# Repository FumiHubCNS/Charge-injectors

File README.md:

# Charge-injectors
Charge injectors for front-end cards

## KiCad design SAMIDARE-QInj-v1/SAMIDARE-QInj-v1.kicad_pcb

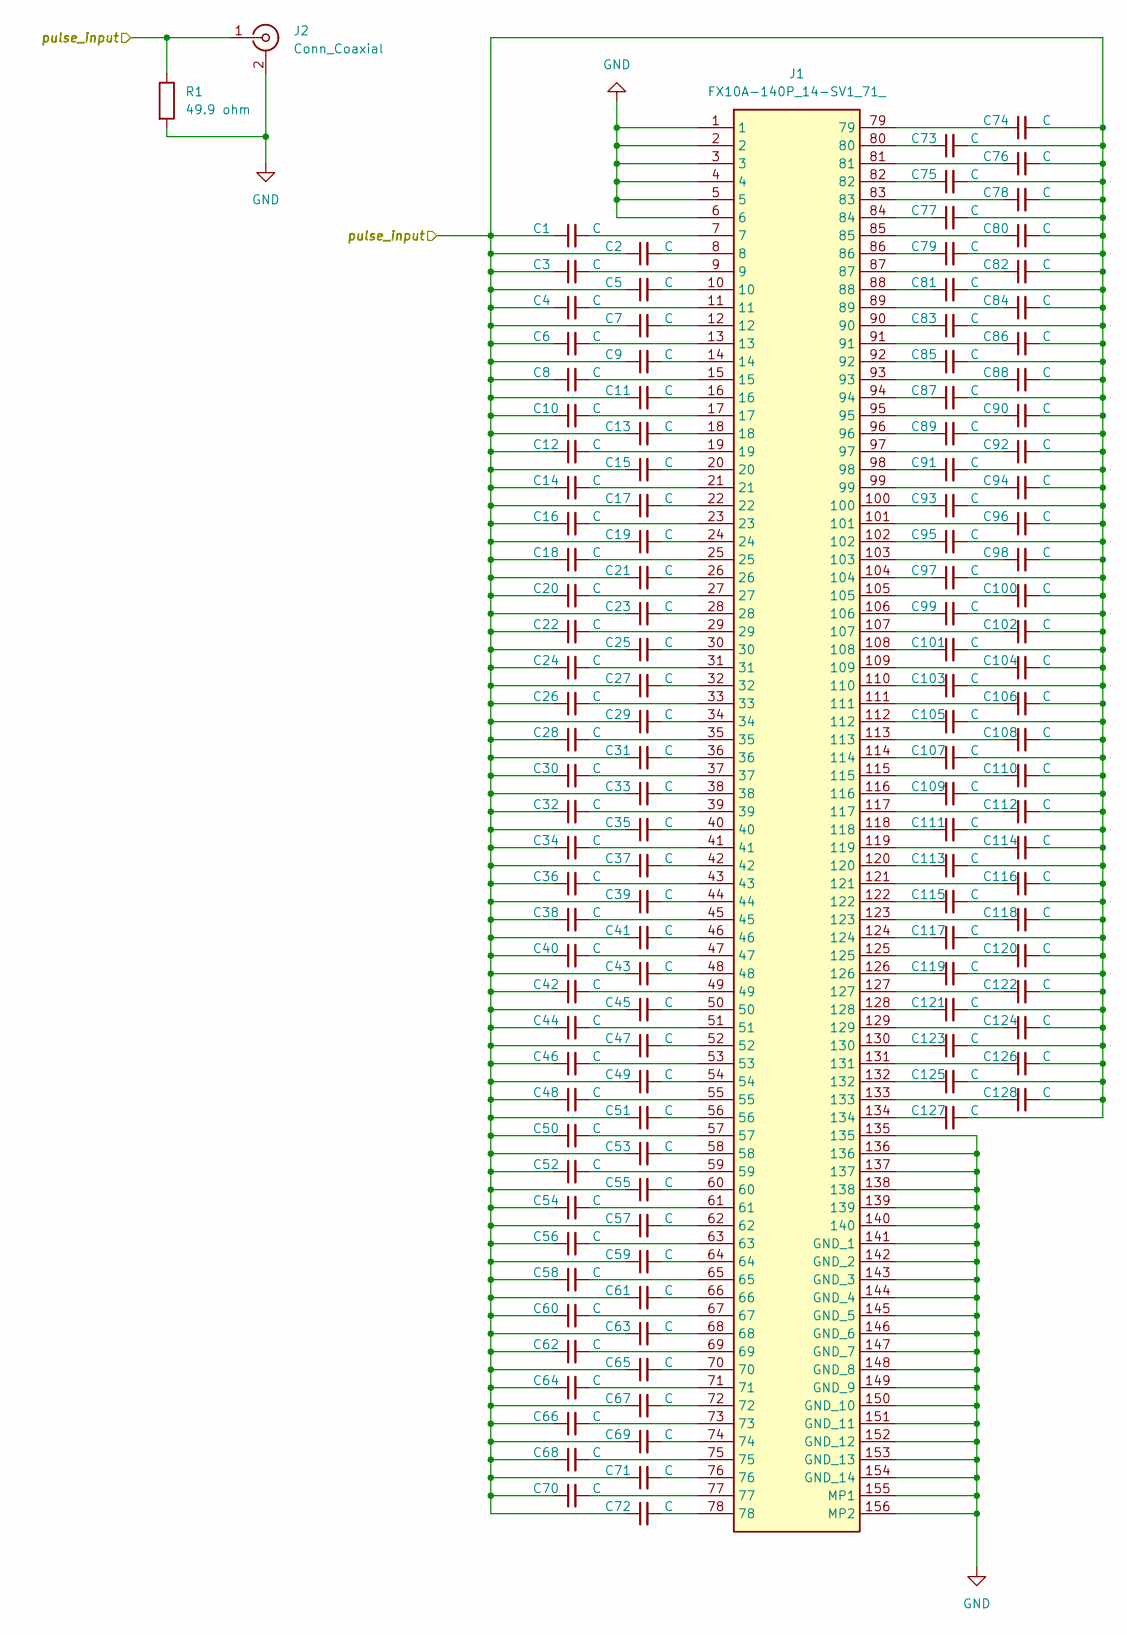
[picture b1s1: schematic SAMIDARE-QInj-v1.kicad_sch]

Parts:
C1, C2, C3, C4, C5, C6, C7, C8, C9, C10, C11, C12, C13, C14, C15, C16, C17, C18, C19, C20, C21, C22, C23, C24, C25, C26, C27, C28, C29, C30, C31, C32, C33, C34, C35, C36, C37, C38, C39, C40, C41, C42, C43, C44, C45, C46, C47, C48, C49, C50, C51, C52, C53, C54, C55, C56, C57, C58, C59, C60, C61, C62, C63, C64, C65, C66, C67, C68, C69, C70, C71, C72, C73, C74, C75, C76, C77, C78, C79, C80, C81, C82, C83, C84, C85, C86, C87, C88, C89, C90, C91, C92, C93, C94, C95, C96, C97, C98, C99, C100, C101, C102, C103, C104, C105, C106, C107, C108, C109, C110, C111, C112, C113, C114, C115, C116, C117, C118, C119, C120, C121, C122, C123, C124, C125, C126, C127, C128: C; C_0402_1005Metric
J1: FX10A-140P_14-SV1_71_; FX10A140P14SV171; Manufacturer_Part_Number FX10A-140P/14-SV1(71); Mouser Part Number 798-FX10A140P14SV171
J2: Conn_Coaxial; MMCX_Molex_73415-0961_Horizontal_1.6mm-PCB
R1: 49.9 ohm; R_0603_1608Metric

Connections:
/pulse_input: C1.1, C2.1, C3.1, C4.1, C5.1, C6.1, C7.1, C8.1, C9.1, C10.1, C11.1, C12.1, C13.1, C14.1, C15.1, C16.1, C17.1, C18.1, C19.1, C20.1, C21.1, C22.1, C23.1, C24.1, C25.1, C26.1, C27.1, C28.1, C29.1, C30.1, C31.1, C32.1, C33.1, C34.1, C35.1, C36.1, C37.1, C38.1, C39.1, C40.1, C41.1, C42.1, C43.1, C44.1, C45.1, C46.1, C47.1, C48.1, C49.1, C50.1, C51.1, C52.1, C53.1, C54.1, C55.1, C56.1, C57.1, C58.1, C59.1, C60.1, C61.1, C62.1, C63.1, C64.1, C65.1, C66.1, C67.1, C68.1, C69.1, C70.1, C71.1, C72.1, C73.2, C74.2, C75.2, C76.2, C77.2, C78.2, C79.2, C80.2, C81.2, C82.2, C83.2, C84.2, C85.2, C86.2, C87.2, C88.2, C89.2, C90.2, C91.2, C92.2, C93.2, C94.2, C95.2, C96.2, C97.2, C98.2, C99.2, C100.2, C101.2, C102.2, C103.2, C104.2, C105.2, C106.2, C107.2, C108.2, C109.2, C110.2, C111.2, C112.2, C113.2, C114.2, C115.2, C116.2, C117.2, C118.2, C119.2, C120.2, C121.2, C122.2, C123.2, C124.2, C125.2, C126.2, C127.2, C128.2, J2.1 (In), R1.1
GND: J1.1, J1.2, J1.3, J1.4, J1.5, J1.6, J1.135, J1.136, J1.137, J1.138, J1.139, J1.140, J1.141 (GND_1), J1.142 (GND_2), J1.143 (GND_3), J1.144 (GND_4), J1.145 (GND_5), J1.146 (GND_6), J1.147 (GND_7), J1.148 (GND_8), J1.149 (GND_9), J1.150 (GND_10), J1.151 (GND_11), J1.152 (GND_12), J1.153 (GND_13), J1.154 (GND_14), J1.155 (MP1), J1.156 (MP2), J2.2 (Ext), R1.2
unnamed: C1.2, J1.7
unnamed: C2.2, J1.8
unnamed: C3.2, J1.9
unnamed: C4.2, J1.11
unnamed: C5.2, J1.10
unnamed: C6.2, J1.13
unnamed: C7.2, J1.12
unnamed: C8.2, J1.15
unnamed: C9.2, J1.14
unnamed: C10.2, J1.17
unnamed: C11.2, J1.16
unnamed: C12.2, J1.19
unnamed: C13.2, J1.18
unnamed: C14.2, J1.21
unnamed: C15.2, J1.20
unnamed: C16.2, J1.23
unnamed: C17.2, J1.22
unnamed: C18.2, J1.25
unnamed: C19.2, J1.24
unnamed: C20.2, J1.27
unnamed: C21.2, J1.26
unnamed: C22.2, J1.29
unnamed: C23.2, J1.28
unnamed: C24.2, J1.31
unnamed: C25.2, J1.30
unnamed: C26.2, J1.33
unnamed: C27.2, J1.32
unnamed: C28.2, J1.35
unnamed: C29.2, J1.34
unnamed: C30.2, J1.37
unnamed: C31.2, J1.36
unnamed: C32.2, J1.39
unnamed: C33.2, J1.38
unnamed: C34.2, J1.41
unnamed: C35.2, J1.40
unnamed: C36.2, J1.43
unnamed: C37.2, J1.42
unnamed: C38.2, J1.45
unnamed: C39.2, J1.44
unnamed: C40.2, J1.47
unnamed: C41.2, J1.46
unnamed: C42.2, J1.49
unnamed: C43.2, J1.48
unnamed: C44.2, J1.51
unnamed: C45.2, J1.50
unnamed: C46.2, J1.53
unnamed: C47.2, J1.52
unnamed: C48.2, J1.55
unnamed: C49.2, J1.54
unnamed: C50.2, J1.57
unnamed: C51.2, J1.56
unnamed: C52.2, J1.59
unnamed: C53.2, J1.58
unnamed: C54.2, J1.61
unnamed: C55.2, J1.60
unnamed: C56.2, J1.63
unnamed: C57.2, J1.62
unnamed: C58.2, J1.65
unnamed: C59.2, J1.64
unnamed: C60.2, J1.67
unnamed: C61.2, J1.66
unnamed: C62.2, J1.69
unnamed: C63.2, J1.68
unnamed: C64.2, J1.71
unnamed: C65.2, J1.70
unnamed: C66.2, J1.73
unnamed: C67.2, J1.72
unnamed: C68.2, J1.75
unnamed: C69.2, J1.74
unnamed: C70.2, J1.77
unnamed: C71.2, J1.76
unnamed: C72.2, J1.78
unnamed: C73.1, J1.80
unnamed: C74.1, J1.79
unnamed: C75.1, J1.82
unnamed: C76.1, J1.81
unnamed: C77.1, J1.84
unnamed: C78.1, J1.83
unnamed: C79.1, J1.86
unnamed: C80.1, J1.85
unnamed: C81.1, J1.88
unnamed: C82.1, J1.87
unnamed: C83.1, J1.90
unnamed: C84.1, J1.89
unnamed: C85.1, J1.92
unnamed: C86.1, J1.91
unnamed: C87.1, J1.94
unnamed: C88.1, J1.93
unnamed: C89.1, J1.96
unnamed: C90.1, J1.95
unnamed: C91.1, J1.98
unnamed: C92.1, J1.97
unnamed: C93.1, J1.100
unnamed: C94.1, J1.99
unnamed: C95.1, J1.102
unnamed: C96.1, J1.101
unnamed: C97.1, J1.104
unnamed: C98.1, J1.103
unnamed: C99.1, J1.106
unnamed: C100.1, J1.105
unnamed: C101.1, J1.108
unnamed: C102.1, J1.107
unnamed: C103.1, J1.110
unnamed: C104.1, J1.109
unnamed: C105.1, J1.112
unnamed: C106.1, J1.111
unnamed: C107.1, J1.114
unnamed: C108.1, J1.113
unnamed: C109.1, J1.116
unnamed: C110.1, J1.115
unnamed: C111.1, J1.118
unnamed: C112.1, J1.117
unnamed: C113.1, J1.120
unnamed: C114.1, J1.119
unnamed: C115.1, J1.122
unnamed: C116.1, J1.121
unnamed: C117.1, J1.124
unnamed: C118.1, J1.123
unnamed: C119.1, J1.126
unnamed: C120.1, J1.125
unnamed: C121.1, J1.128
unnamed: C122.1, J1.127
unnamed: C123.1, J1.130
unnamed: C124.1, J1.129
unnamed: C125.1, J1.132
unnamed: C126.1, J1.131
unnamed: C127.1, J1.134
unnamed: C128.1, J1.133

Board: 2 copper layers, 131 parts (1 on the bottom side), 130 nets, no tracks yet.

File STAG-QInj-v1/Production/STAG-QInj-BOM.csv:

Designator,Footprint,Quantity,Comment,LCSC Part #
"J1","SAMTEC_QTE-040-01-L-D-A",1,"QTE-040-01-L-D-A",C3642632
"C17,C14,C32,C16,C2,C11,C64,C20,C10,C4,C38,C5,C63,C7,C59,C61,C50,C18,C13,C34,C19,C54,C24,C51,C15,C42,C60,C45,C23,C41,C28,C46,C29,C9,C27,C36,C49,C56,C53,C40,C55,C52,C62,C35,C48,C6,C57,C39,C21,C8,C22,C58,C26,C12,C1,C33,C47,C25,C43,C44,C3,C30,C31,C37","C_0402_1005Metric",64,"1pF, 1005, Tolerance +- 10%",C76953
"R1","R_0603_1608Metric",1,"49.9Ω, 1608, Tolerance +- 1%",C23185
"J2","SAMTEC_MMCX-J-P-H-ST-EM1",1,"MMCX",C5670146

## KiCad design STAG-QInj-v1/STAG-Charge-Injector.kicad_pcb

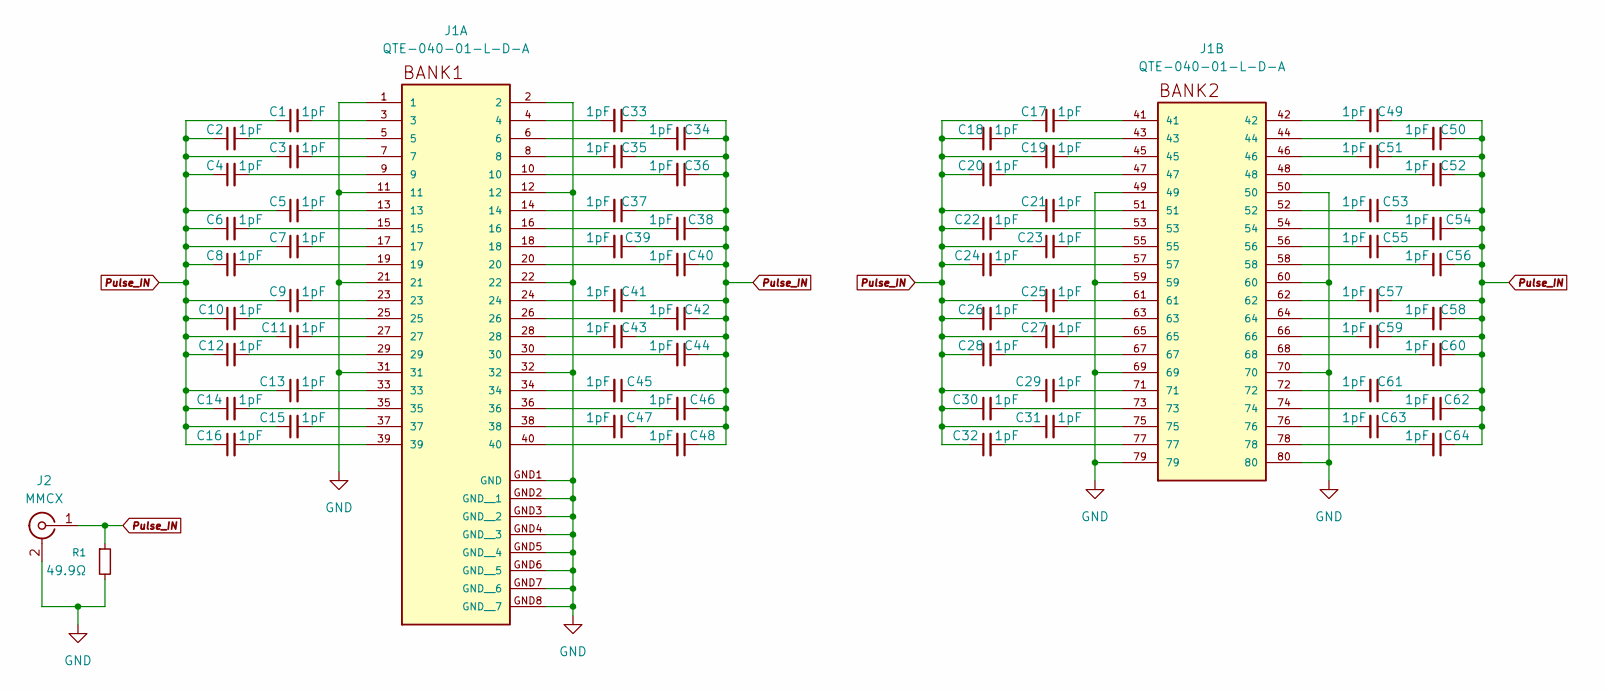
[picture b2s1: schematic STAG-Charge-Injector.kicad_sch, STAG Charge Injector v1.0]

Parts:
C1, C2, C3, C4, C5, C6, C7, C8, C9, C10, C11, C12, C13, C14, C15, C16, C17, C18, C19, C20, C21, C22, C23, C24, C25, C26, C27, C28, C29, C30, C31, C32, C33, C34, C35, C36, C37, C38, C39, C40, C41, C42, C43, C44, C45, C46, C47, C48, C49, C50, C51, C52, C53, C54, C55, C56, C57, C58, C59, C60, C61, C62, C63, C64: 1pF; C_0402_1005Metric
J1: QTE-040-01-L-D-A; SAMTEC_QTE-040-01-L-D-A; PARTREV CM
J2: MMCX; SAMTEC_MMCX-J-P-H-ST-EM1
R1: 49.9Ω; R_0603_1608Metric

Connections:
GND: J1.1, J1.2, J1.11, J1.12, J1.21, J1.22, J1.31, J1.32, J1.49, J1.50, J1.59, J1.60, J1.69, J1.70, J1.79, J1.80, J1.GND1 (GND), J1.GND2 (GND__1), J1.GND3 (GND__2), J1.GND4 (GND__3), J1.GND5 (GND__4), J1.GND6 (GND__5), J1.GND7 (GND__6), J1.GND8 (GND__7), J2.2 (Ext), J2.S1, J2.S2, R1.2
unnamed: C1.2, J1.3
unnamed: C2.2, J1.5
unnamed: C3.2, J1.7
unnamed: C4.2, J1.9
unnamed: C5.2, J1.13
unnamed: C6.2, J1.15
unnamed: C7.2, J1.17
unnamed: C8.2, J1.19
unnamed: C9.2, J1.23
unnamed: C10.2, J1.25
unnamed: C11.2, J1.27
unnamed: C12.2, J1.29
unnamed: C13.2, J1.33
unnamed: C14.2, J1.35
unnamed: C15.2, J1.37
unnamed: C16.2, J1.39
unnamed: C17.2, J1.41
unnamed: C18.2, J1.43
unnamed: C19.2, J1.45
unnamed: C20.2, J1.47
unnamed: C21.2, J1.51
unnamed: C22.2, J1.53
unnamed: C23.2, J1.55
unnamed: C24.2, J1.57
unnamed: C25.2, J1.61
unnamed: C26.2, J1.63
unnamed: C27.2, J1.65
unnamed: C28.2, J1.67
unnamed: C29.2, J1.71
unnamed: C30.2, J1.73
unnamed: C31.2, J1.75
unnamed: C32.2, J1.77
unnamed: C33.2, J1.4
unnamed: C34.2, J1.6
unnamed: C35.2, J1.8
unnamed: C36.2, J1.10
unnamed: C37.2, J1.14
unnamed: C38.2, J1.16
unnamed: C39.2, J1.18
unnamed: C40.2, J1.20
unnamed: C41.2, J1.24
unnamed: C42.2, J1.26
unnamed: C43.2, J1.28
unnamed: C44.2, J1.30
unnamed: C45.2, J1.34
unnamed: C46.2, J1.36
unnamed: C47.2, J1.38
unnamed: C48.2, J1.40
unnamed: C49.2, J1.42
unnamed: C50.2, J1.44
unnamed: C51.2, J1.46
unnamed: C52.2, J1.48
unnamed: C53.2, J1.52
unnamed: C54.2, J1.54
unnamed: C55.2, J1.56
unnamed: C56.2, J1.58
unnamed: C57.2, J1.62
unnamed: C58.2, J1.64
unnamed: C59.2, J1.66
unnamed: C60.2, J1.68
unnamed: C61.2, J1.72
unnamed: C62.2, J1.74
unnamed: C63.2, J1.76
unnamed: C64.2, J1.78
Pulse_IN: C1.1, C2.1, C3.1, C4.1, C5.1, C6.1, C7.1, C8.1, C9.1, C10.1, C11.1, C12.1, C13.1, C14.1, C15.1, C16.1, C17.1, C18.1, C19.1, C20.1, C21.1, C22.1, C23.1, C24.1, C25.1, C26.1, C27.1, C28.1, C29.1, C30.1, C31.1, C32.1, C33.1, C34.1, C35.1, C36.1, C37.1, C38.1, C39.1, C40.1, C41.1, C42.1, C43.1, C44.1, C45.1, C46.1, C47.1, C48.1, C49.1, C50.1, C51.1, C52.1, C53.1, C54.1, C55.1, C56.1, C57.1, C58.1, C59.1, C60.1, C61.1, C62.1, C63.1, C64.1, J2.1 (In), R1.1

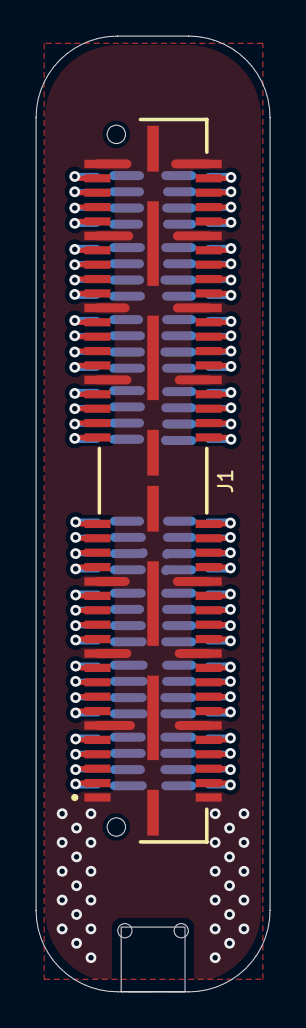
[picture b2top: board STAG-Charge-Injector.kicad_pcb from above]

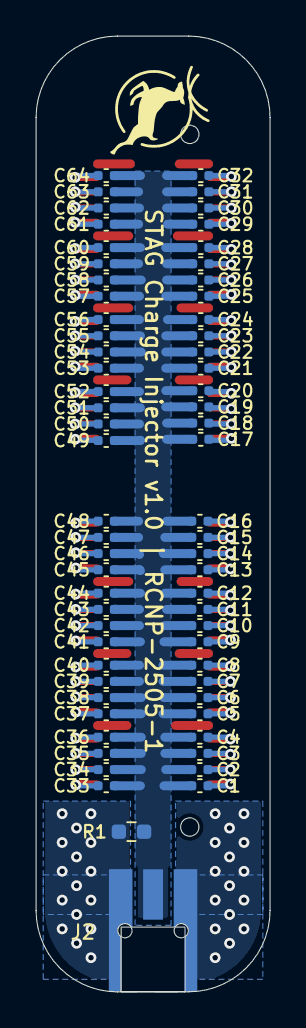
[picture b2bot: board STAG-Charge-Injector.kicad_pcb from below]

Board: 2 copper layers, 13.0 x 53.1 mm, 67 parts (66 on the bottom side), 66 nets.

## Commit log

2026-06-02 Add the design and production files for STAG charge injector v1
2026-06-03 generate samidare charge injector version 0
